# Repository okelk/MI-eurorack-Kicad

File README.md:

This a fork of the Mutable Instruments Eurorack repository.
The original files are all made in EAGLE. Because Autodesk will no longer sell nor support EAGLE effective June 7, 2026 this repository aims to archive them in a more future-proof format for KiCad.

All 'pcb' filders contain subfolders with the original files, versions converted to the older EAGLE v7 format that is needed for the KiCAD import functionality, and Versions in KiCad format.

As of 2026-06-03 those files might not be complete and are untested.
The KiCad importer for EAGLE is quite good but do expect small errors. It looks like all oval holes got lost!

I added [cvpal](https://github.com/pichenettes/cvpal) to this repository for completeness sake, it is not originally part of the MI eurorack repository.

Mutable Instruments' Eurorack Modules.

* [Blades](http://mutable-instruments.net/modules/blades): Dual multimode filter.
* [Blinds](http://mutable-instruments.net/modules/blinds): Quad VC-polarizer.
* [Braids](http://mutable-instruments.net/modules/braids): Macro-oscillator.
* [Branches](http://mutable-instruments.net/modules/branches): Dual Bernoulli gate.
* [Clouds](http://mutable-instruments.net/modules/clouds): Texture synthesizer.
* [Ears](http://mutable-instruments.net/modules/ears): Contact microphone.
* [Edges](http://mutable-instruments.net/modules/edges): Quad chiptune digital oscillator.
* [Elements](http://mutable-instruments.net/modules/elements): Modal synthesizer.
* [Frames](http://mutable-instruments.net/modules/frames): Keyframer/mixer.
* [Grids](http://mutable-instruments.net/modules/grids): Topographic drum sequencer.
* [Kinks](http://mutable-instruments.net/modules/kinks): Utility module - rectifier, analog logic, S&H, noise.
* [Links](http://mutable-instruments.net/modules/links): Utility module - buffer, mixer.
* [Marbles](http://mutable-instruments.net/modules/marbles): Random sampler.
* [Peaks](http://mutable-instruments.net/modules/peaks): Dual trigger converter.
* [Plaits](http://mutable-instruments.net/modules/plaits): Macro oscillator.
* [Rings](http://mutable-instruments.net/modules/rings): Resonator.
* [Ripples](http://mutable-instruments.net/modules/ripples): Liquid 2-pole BP, 2-pole LP and 4-pole LP filter.
* [Shades](http://mutable-instruments.net/modules/shades): Triple attenuverter.
* [Shelves](http://mutable-instruments.net/modules/shelves): EQ filter.
* [Stages](http://mutable-instruments.net/modules/stages): Segment generator.
* [Streams](http://mutable-instruments.net/modules/streams): Dual dynamics gate.
* [Tides](http://mutable-instruments.net/modules/tides): Tidal modulator.
* [Veils](http://mutable-instruments.net/modules/veils): Quad VCA.
* [Volts](http://mutable-instruments.net/modules/volts): +5V power module.
* [Warps](http://mutable-instruments.net/modules/warps): Meta-modulator.
* [Yarns](http://mutable-instruments.net/modules/yarns): MIDI interface.

License
=======

Code (AVR projects): GPL3.0.

Code (STM32F projects): MIT license.

Hardware: cc-by-sa-3.0

By: Emilie Gillet (emilie.o.gillet@gmail.com)

Guidelines for derivative works
===============================

**Mutable Instruments is a registered trademark.**

The name "Mutable Instruments" should not be used on any of the derivative works you create from these files.

We do not recommend you to keep the original name of the Mutable Instruments module for your derivative works.

For example, your 5U adaptation of Mutable Instruments Clouds can be called "Foobar Modular - Particle Generator".

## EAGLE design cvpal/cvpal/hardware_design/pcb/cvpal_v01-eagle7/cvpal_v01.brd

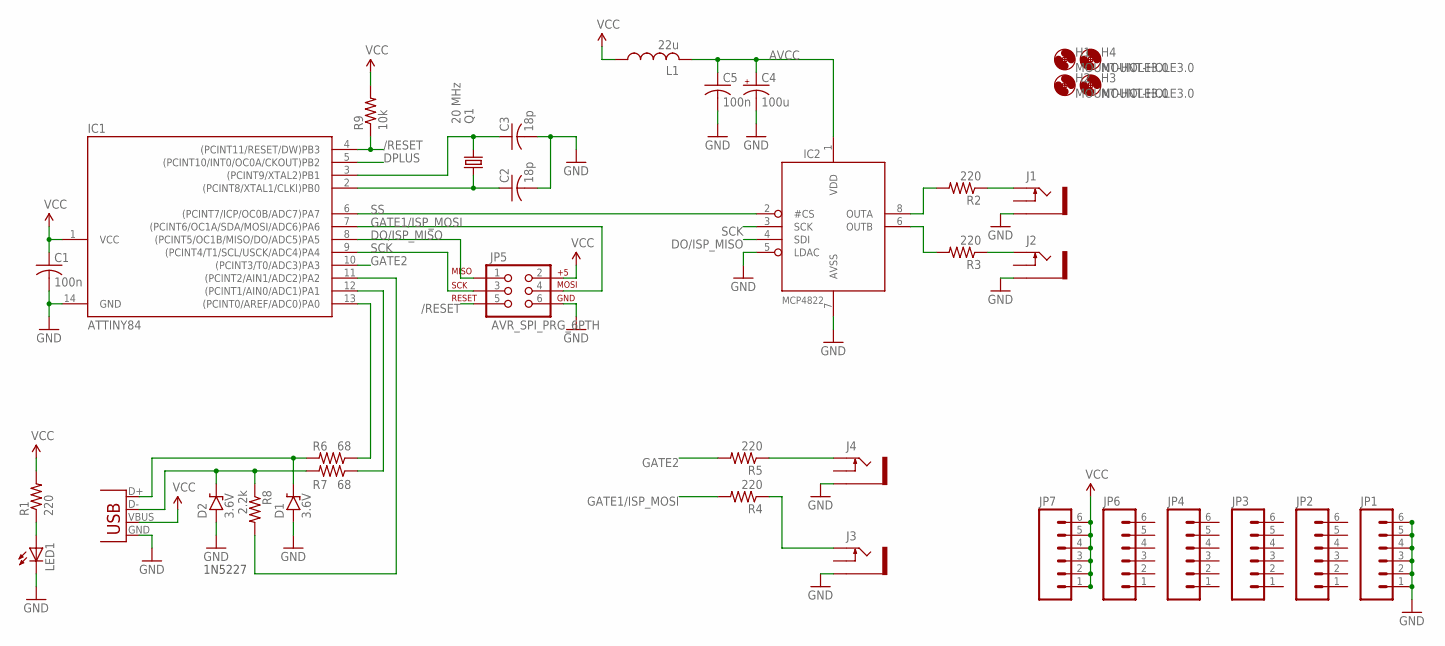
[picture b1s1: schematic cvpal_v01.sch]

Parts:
C1, C5: 100n; C025-025X050
C2, C3: 18p; C025-025X050
C4: 100u; E2,5-7
D1, D2: 3.6V; D-5
H1, H2, H3, H4: MOUNT-HOLE3.0; 3,0
IC1: ATTINY84; DIL14
IC2: MCP4822; DIL08
J1, J2, J3, J4: 1503_12
JP1, JP2, JP3, JP4, JP6, JP7: M06SIP; 1X06
JP5: AVR_SPI_PRG_6PTH; 2X3
L1: 22u; 0207/10
LED1: LED5MM
Q1: 20 MHz; HC49/S
R1, R2, R3, R4, R5: 220; 0204/7
R6, R7: 68; 0204/7
R8: 2.2k; 0204/7
R9: 10k; 0204/7
X2: USBPTH; USB-B-PTH

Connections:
/RESET: IC1.4 ((PCINT11/RESET/DW)PB3), JP5.5, R9.1
AVCC: C4.+, C5.1, IC2.1 (VDD), L1.2
CV1: IC2.8 (OUTA), R2.2
CV1_R: J1.3 (2), R2.1
CV2: IC2.6 (OUTB), R3.2
D+: D1.C, R6.2, X2.D+
D-: D2.C, R7.2, R8.1, X2.D-
DMINUS: IC1.12 ((PCINT1/AIN0/ADC1)PA1), R7.1
DO/ISP_MISO: IC1.8 ((PCINT5/OC1B/MISO/DO/ADC5)PA5), IC2.4 (SDI), JP5.1
DPLUS: IC1.5 ((PCINT10/INT0/OC0A/CKOUT)PB2), IC1.13 ((PCINT0/AREF/ADC0)PA0), R6.1
GATE1/ISP_MOSI: IC1.7 ((PCINT6/OC1A/SDA/MOSI/ADC6)PA6), JP5.4, R4.2
GATE2: IC1.10 ((PCINT3/T0/ADC3)PA3), R5.2
GND: C1.2, C2.2, C3.2, C4.-, C5.2, D1.A, D2.A, IC1.14 (GND), IC2.5 (LDAC), IC2.7 (AVSS), J1.5 (1), J2.5 (1), J3.5 (1), J4.5 (1), JP1.1, JP1.2, JP1.3, JP1.4, JP1.5, JP1.6, JP5.6, LED1.K (C), X2.GND
unnamed: LED1.A, R1.1
unnamed: C3.1, IC1.3 ((PCINT9/XTAL2)PB1), Q1.1
unnamed: C2.1, IC1.2 ((PCINT8/XTAL1/CLKI)PB0), Q1.2
unnamed: J2.3 (2), R3.1
unnamed: J4.3 (2), R5.1
unnamed: IC1.11 ((PCINT2/AIN1/ADC2)PA2), R8.2
unnamed: J3.3 (2), R4.1
SCK: IC1.9 ((PCINT4/T1/SCL/USCK/ADC4)PA4), IC2.3 (SCK), JP5.3
SS: IC1.6 ((PCINT7/ICP/OC0B/ADC7)PA7), IC2.2 (#CS)
VCC: C1.1, IC1.1 (VCC), JP5.2, JP7.1, JP7.2, JP7.3, JP7.4, JP7.5, JP7.6, L1.1, R1.2, R9.2, X2.VBUS

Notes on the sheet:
1N5227

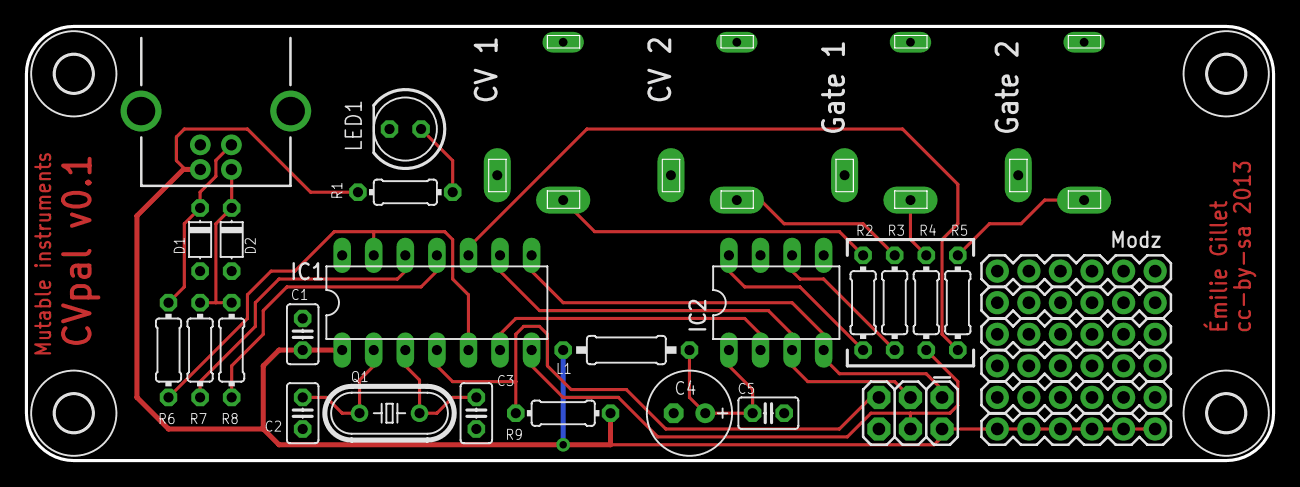
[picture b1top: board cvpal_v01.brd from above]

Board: 2 copper layers, 100.3 x 34.9 mm, 37 parts (0 on the bottom side), 23 nets.

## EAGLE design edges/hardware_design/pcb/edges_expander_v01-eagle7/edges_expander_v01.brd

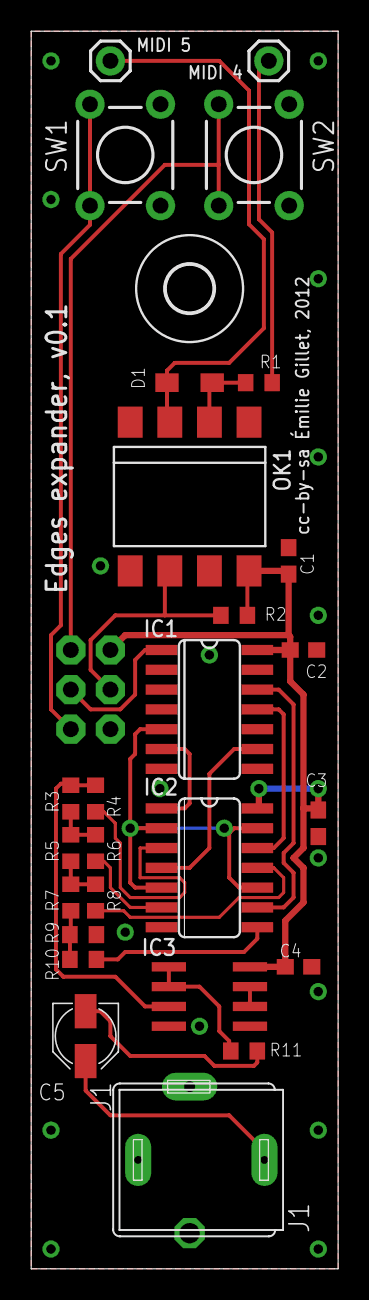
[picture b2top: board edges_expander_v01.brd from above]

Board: 2 copper layers, 19.7 x 79.4 mm, 28 parts (1 on the bottom side), 26 nets.

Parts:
C1, C2, C3, C4: 100n; C0603
C5: 10u; PANASONIC_B
D1: 1N4148; SOD323-W
IC1: 4024D; SO14
IC2: 74LS86D; SO14
IC3: AD8532; SO08
J1: PJ301WQP; WQP_PJ_301BM
J2: 2X3
JP1, JP2: M01PTH; 1X01
OK1: 6N137; DIL8-SMD
R1: 220; R0603
R2: 4.7k; R0603
R3, R5, R7: 10k; R0603
R4, R6, R8, R9, R10: 20k; R0603
R11: 1k; R0603
SW1, SW2: TACTILE-PTH
U$1: 3,0

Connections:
+3V3_EXP: C1.1, C2.1, C3.1, C4.1, IC1.14, IC2.14, IC3.8, J2.1, OK1.8, R2.2
GND: C1.2, C2.2, C3.2, C4.2, IC1.2, IC1.7, IC2.7, IC3.4, IC3.5, J1.GND, J1.GND2, J2.5, OK1.5, R9.1, SW1.1, SW1.2, SW2.1, SW2.2
MIDI_IN: J2.3, OK1.6, R2.1
MIDI_IN4: JP2.1, R1.1
MIDI_IN5: D1.A, JP1.1, OK1.3
MIDI_LEARN: J2.2, SW2.3, SW2.4
MIDI_MODE: J2.6, SW1.3, SW1.4
unnamed: IC2.3, R4.2
unnamed: IC2.6, R6.2
unnamed: IC2.11, R8.2
unnamed: IC2.8, R10.2
unnamed: D1.C, OK1.2, R1.2
unnamed: IC1.5, IC2.2, IC2.5, IC2.10, IC2.13
unnamed: IC1.9, IC2.4
unnamed: IC1.11, IC2.12
unnamed: IC1.12, IC2.9
unnamed: IC3.6, IC3.7
unnamed: IC1.6, IC2.1
unnamed: R7.1, R9.2, R10.1
unnamed: R5.1, R7.2, R8.1
unnamed: R3.1, R5.2, R6.1
unnamed: IC3.3, R3.2, R4.1
unnamed: C5.-, R11.1
unnamed: IC3.1, IC3.2, R11.2
unnamed: C5.+, J1.TIP
TRIANGLE: IC1.1, J2.4

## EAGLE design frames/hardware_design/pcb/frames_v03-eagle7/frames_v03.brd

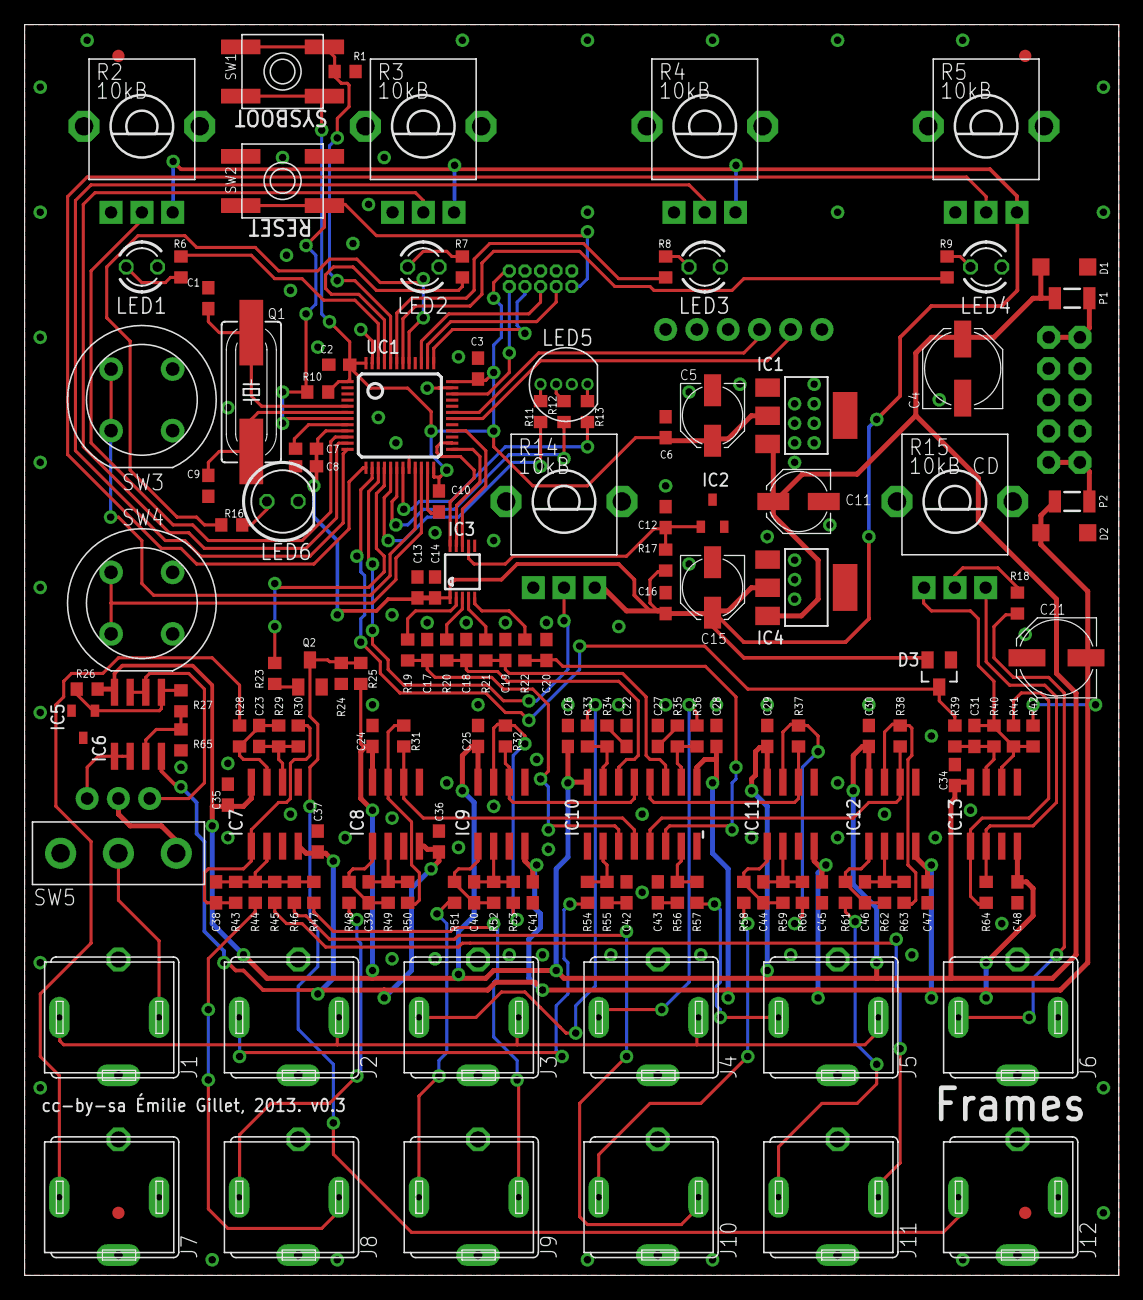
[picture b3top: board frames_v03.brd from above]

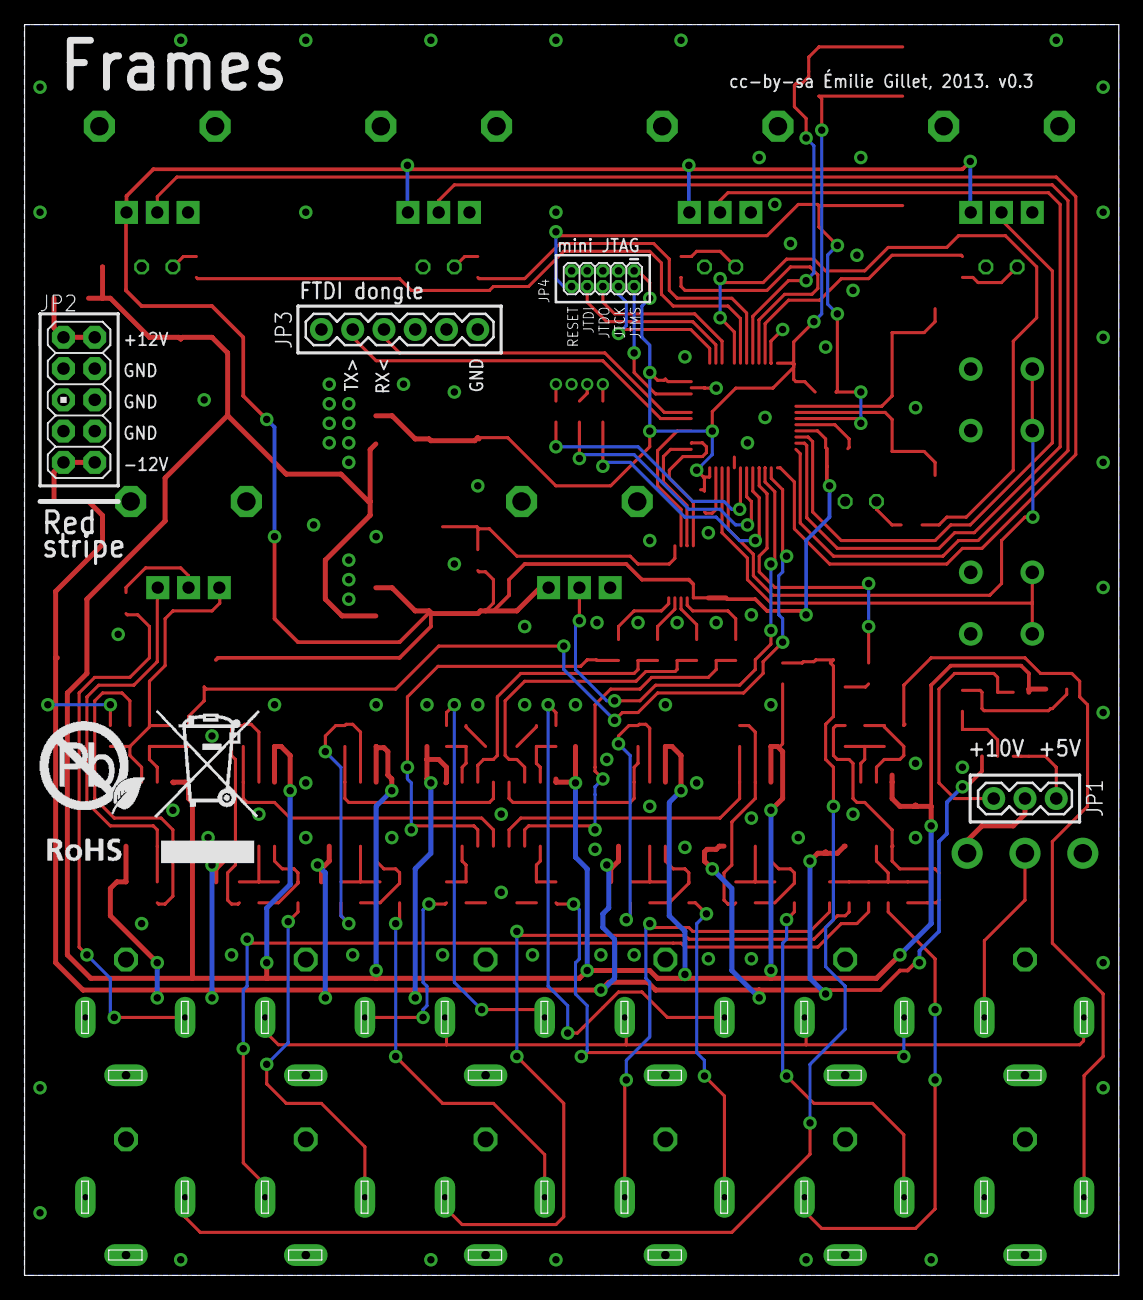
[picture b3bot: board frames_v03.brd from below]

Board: 2 copper layers, 88.9 x 101.6 mm, 165 parts (5 on the bottom side), 110 nets.

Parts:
C1, C9, C23, C38, C39, C40, C44, C46: 18p; C0603
C2, C3, C6, C7, C10, C13, C16, C24, C25, C26, C28, C29, C30, C34, C35, C36, C37, C41, C45, C47, C48: 100n; C0603
C4, C21: 47u; PANASONIC_D
C5, C11, C15: 22u; PANASONIC_C
C8, C14: 3.3u; C0603
C12: 470n; C0603
C17, C18, C19, C20: 1u; C0603
C22, C27, C31, C42, C43: 560p; C0603
D1, D2: 1N5819HW; SOD123
D3: BAT54S; SOT23
F1, F2, F3, F4: FIDUCIAL1X2; FIDUCIAL-1X2
IC1, IC4: LM1117-3.3; SOT223
IC2: LM4040B25; DBZ_R-PDSO-G3
IC3: DAC124S085CIMT; MSOP10
IC5: LM4040B10; DBZ_R-PDSO-G3
IC6, IC7, IC8, IC9, IC11, IC12, IC13: TL072D; SO08
IC10: V2164SZ; SOIC16N
J1, J2, J3, J4, J5, J6, J7, J8, J9, J10, J11, J12: PJ301WQP; WQP_PJ_301BM
JP1: 1X03
JP2: M05X2PTH; AVR_ICSP
JP3: 1X06
JP4: M05X2MINIJTAG; 2X5-1.27
LED1, LED2, LED3, LED4: WP710A10GD; LED3MM
LED5: WP154A4SUREQBFZG; LED-TRICOLOR-THROUGHHOLE
LED6: WP7113SGD; LED5MM
P1, P2: PTCSMD; PTC-1206
Q1: 8MHz; HC49UP
Q2: MMBT3904; SOT23-BEC
R1, R10, R23: 10k; R0603
R2, R3, R4, R5, R14: 10kB; ALPS_POT_VERTICAL_PS
R6, R7, R8, R9, R11, R12, R13, R16, R19, R20, R21, R22: 100; R0603
R15: 10kB CD; ALPS_POT_VERTICAL_PS
R17, R34, R35, R55, R56: 510; R0603
R18, R27, R29, R30, R31, R32, R33, R36, R37, R38, R41, R44, R45, R46, R47, R49, R50, R52, R53, R54, R57, R59, R60, R62, R63, R64, R65: 100k; R0603
R24: 3.3k; R0603
R25, R26: 4.7k; R0603
R28, R39, R48, R51, R58, R61: 1.0k; R0603
R40: 33k; R0603
R42: 240k; R0603
R43: 49.9k; R0603
SW1, SW2: EVQ-Q2
SW3, SW4: D6R
SW5: ES_100SP1T6B11M2QEH_SMALL
U$1: EURORACK_TEMPLATE
U$3: ROHS_BIG
UC1: STM32F103CBT6; LQFP48

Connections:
+3V3: C2.1, C3.1, C5.+, C6.1, C10.1, IC1.2, JP4.1, R10.2, SW1.B, SW1.B', UC1.1, UC1.24, UC1.36, UC1.48
+3V3_A: C7.1, C8.1, C13.1, C14.1, C15.+, C16.1, D3.2, IC3.1, IC4.2, R2.P$1, R3.P$1, R4.P$1, R5.P$1, R14.P$1, R17.1, UC1.9
ADD_SWITCH: SW3.A1, SW3.A2, UC1.21
AREF_2.5: C12.1, IC2.1, IC3.7, R17.2
AREF_5: IC6.1, IC6.2, JP1.1
AREF_10: IC6.6, IC6.7, JP1.3
AREF_10_0: IC5.1, IC6.5, R26.2, R27.2
BOOT_FLASH: R1.2, SW1.A, SW1.A', UC1.44
DAC_MOSI: IC3.8, UC1.28
DAC_SCK: IC3.10, UC1.26
DAC_SS: IC3.9, UC1.25
DEL_SWITCH: SW4.A1, SW4.A2, UC1.22
FB_CURRENT: IC10.2, R54.2, R55.2
FB_CURRENT1: IC10.15, R33.2, R34.2
FB_CURRENT2: IC10.10, R35.2, R36.2
FB_CURRENT3: IC10.7, R56.2, R57.2
FRAME_CHANGE: R23.1, UC1.16
GAIN_1: C17.1, IC10.3, R19.2
GAIN_2: C18.1, IC10.14, R20.2
GAIN_3: C19.1, IC10.11, R21.2
GAIN_4: C20.1, IC10.6, R22.2
GATE2_LED: LED3.A, R8.2
GATE3_LED: LED2.A, R7.2
GATE4_LED: LED1.A, R6.2
GND: C1.1, C2.2, C3.2, C4.-, C5.-, C6.2, C7.2, C8.2, C9.1, C10.2, C11.-, C12.2, C13.2, C14.2, C15.-, C16.2, C17.2, C18.2, C19.2, C20.2, C21.+, C22.2, C24.2, C25.2, C26.2, C27.2, C28.1, C29.2, C30.2, C34.2, C35.2, C36.1, C37.1, C41.1, C42.2, C43.2, C45.1, C47.1, C48.1, D1.A, D2.C, D3.1, IC1.1, IC2.2, IC3.6, IC4.1, IC5.2, IC7.3, IC7.5, IC8.3, IC8.5, IC9.3, IC9.5, IC10.8, IC11.3, IC11.5, IC12.3, IC12.5, IC13.3, IC13.5, J1.GND, J1.GND2, J2.GND, J2.GND2, J3.GND, J3.GND2, J4.GND, J4.GND2, J5.GND, J5.GND2, J6.GND, J6.GND2, J7.GND, J7.GND2, J8.GND, J8.GND2, J9.GND, J9.GND2, J10.GND, J10.GND2, J11.GND, J11.GND2, J12.GND, J12.GND2, JP2.3, JP2.4, JP2.5, JP2.6, JP2.7, JP2.8, JP3.1, JP4.3, JP4.5, JP4.9, LED1.K, LED2.K, LED3.K, LED4.K, LED5.GND, LED6.K, Q2.E, R1.1, R2.P$3, R3.P$3, R4.P$3, R5.P$3, R14.P$3, R24.1, R65.1, SW2.A, SW2.A', SW3.B1, SW3.B2, SW4.B1, SW4.B2, SW5.O, UC1.8, UC1.20, UC1.23, UC1.35, UC1.47
IN_1: J2.TIP, R54.1
IN_2: J3.TIP, R33.1
IN_3: J4.TIP, R36.1
IN_4: J5.TIP, R57.1
JTCK: JP4.4, UC1.37
JTDI: JP4.8, UC1.38
JTDO: JP4.6, UC1.39
JTMS: JP4.2, UC1.34
LED_B: R12.1, UC1.18
LED_CH1: R6.1, UC1.46
LED_CH2: R7.1, UC1.45
LED_CH3: R8.1, UC1.43
LED_CH4: R9.1, UC1.42
LED_FRAME: R16.1, UC1.41
LED_G: R11.1, UC1.17
LED_R: R13.1, UC1.19
MODULATION: D3.3, R39.1, UC1.14
unnamed: IC13.2, R15.P$1, R64.2
unnamed: C42.1, R55.1
unnamed: J7.TIP, R28.2
unnamed: IC9.7, R32.2, R53.1
unnamed: R15.P$2, R18.2
unnamed: LED4.A, R9.2
unnamed: C1.2, Q1.2, UC1.5
unnamed: C9.2, Q1.1, UC1.6
unnamed: IC13.1, R41.2, R64.1
unnamed: C27.1, R35.1
unnamed: J6.TIP, R18.1
unnamed: IC8.6, IC10.4, R31.1
unnamed: C31.2, IC13.7, R39.2, R40.1
unnamed: C31.1, IC13.6, R15.P$3, R40.2, R41.1, R42.1
unnamed: C39.1, IC8.2, R49.1, R50.2
unnamed: C39.2, IC8.1, R48.1, R49.2
unnamed: C23.2, IC7.7, R28.1, R29.2
unnamed: C22.1, R34.1
unnamed: C38.1, IC7.2, R43.1, R44.2, R45.2, R46.2, R47.2
unnamed: IC9.6, IC10.13, R32.1
unnamed: C23.1, IC7.6, R29.1, R30.2
unnamed: C40.1, IC9.2, R52.1, R53.2
unnamed: C40.2, IC9.1, R51.1, R52.2
unnamed: IC10.12, IC11.6, R37.1
unnamed: LED6.A, R16.2
unnamed: C44.1, IC11.2, R59.1, R60.2
unnamed: C44.2, IC11.1, R58.1, R59.2
unnamed: C43.1, R56.1
unnamed: C38.2, IC7.1, R30.1, R43.2
unnamed: IC10.5, IC12.6, R38.1
unnamed: IC6.3, R27.1, R65.2
unnamed: C46.1, IC12.2, R62.1, R63.2
unnamed: C46.2, IC12.1, R61.1, R62.2
unnamed: J1.SW, SW5.P
unnamed: LED5.RED, R13.2
unnamed: LED5.BLU, R12.2
unnamed: LED5.GRN, R11.2
unnamed: IC3.2, R19.1
unnamed: J8.TIP, R48.2
unnamed: IC3.3, R20.1
unnamed: JP1.2, SW5.S
unnamed: IC3.4, R21.1
unnamed: J12.TIP, Q2.C, R24.2, R25.1
unnamed: IC3.5, R22.1
unnamed: Q2.B, R23.2
unnamed: IC12.7, R38.2, R63.1
unnamed: J9.TIP, R51.2
unnamed: J11.TIP, R61.2
unnamed: J10.TIP, R58.2
unnamed: JP2.1, JP2.2, P1.2
unnamed: JP2.9, JP2.10, P2.2
PAN: J1.TIP, J2.SW, J3.SW, J4.SW, J5.SW
POT_CH1: R2.P$2, UC1.10
POT_CH2: R3.P$2, UC1.11
POT_CH3: R4.P$2, UC1.12
POT_CH4: R5.P$2, UC1.13
POT_FRAME: R14.P$2, UC1.15
RESET: JP4.10, R10.1, SW2.B, SW2.B', UC1.7
RX: JP3.4, UC1.31
TX: JP3.5, UC1.30
VCA0_1: IC8.7, R31.2, R50.1
VCA0_3: IC11.7, R37.2, R60.1
VCA_1: J8.SW, R44.1
VCA_2: J9.SW, R47.1
VCA_3: J10.SW, R46.1
VCA_4: J11.SW, R45.1
VCC: C4.+, C11.+, C24.1, C25.1, C26.1, C29.1, C30.1, C34.1, C35.1, D1.C, IC1.3, IC4.3, IC6.8, IC7.8, IC8.8, IC9.8, IC10.16, IC11.8, IC12.8, IC13.8, P1.1, R25.2, R26.1
VEE: C21.-, C28.2, C36.2, C37.2, C41.2, C45.2, C47.2, C48.2, D2.A, IC6.4, IC7.4, IC8.4, IC9.4, IC10.9, IC11.4, IC12.4, IC13.4, P2.1, R42.2

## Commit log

2026-06-03 added original versions
    added versions of pre-2020 rippes, shades,veils and pre-2018 tides
2026-06-03 added kicad 7 files
2026-06-03 comment oval holes
2026-06-03 added kicad files
    converted with Kicad 10. Auto-match layers

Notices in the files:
cvpal/cvpal/hardware_design/pcb/cvpal_v01-eagle7/cvpal_v01.brd:
cc-by-sa 2013
edges/hardware_design/pcb/edges_expander_v01-eagle7/edges_expander_v01.brd:
cc-by-sa Émilie Gillet, 2012
frames/hardware_design/pcb/frames_v03-eagle7/frames_v03.brd:
cc-by-sa Émilie Gillet, 2013. v0.3
